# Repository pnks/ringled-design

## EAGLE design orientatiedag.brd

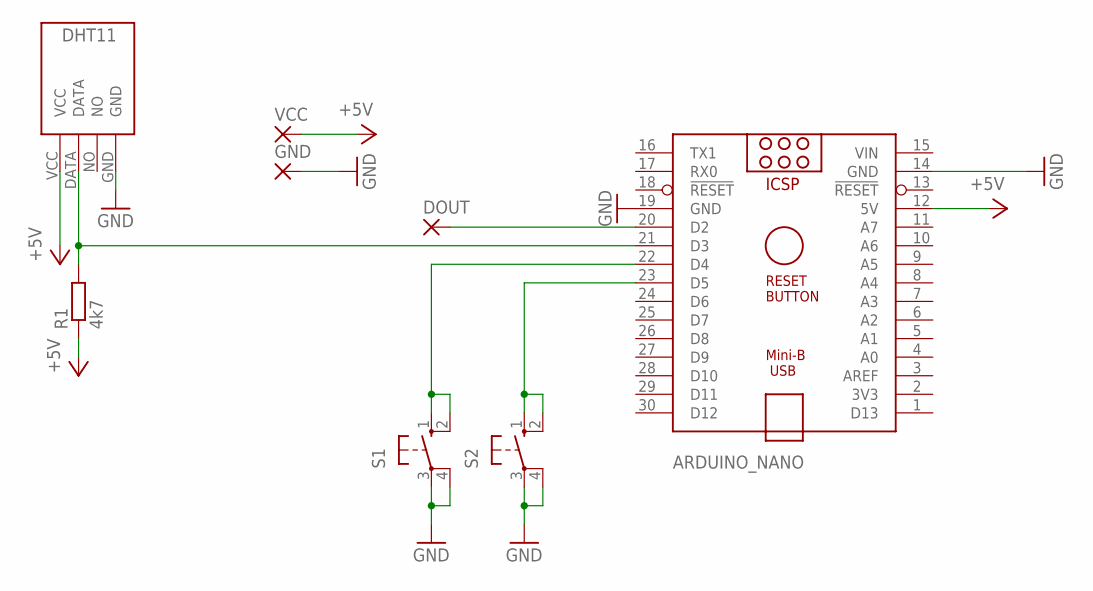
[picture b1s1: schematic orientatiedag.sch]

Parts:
ARDUINO_NANO: ARDUINO_NANO
DOUT: 2,15/1,0
GND: 2,15/1,0
R1: 4k7; 0207/7
S1, S2: 10-XX; B3F-10XX
U$1: DHT11-PION.
VCC: 2,15/1,0

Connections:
+5V: ARDUINO_NANO.12 (5V), R1.1, U$1.VCC, VCC.1
DHT-DATA: ARDUINO_NANO.21 (D3), R1.2, U$1.DATA
GND: ARDUINO_NANO.14 (GND), ARDUINO_NANO.19 (GND), GND.1, S1.3, S1.4 (P1), S2.3, S2.4 (P1), U$1.GND
unnamed: ARDUINO_NANO.22 (D4), S1.1 (S), S1.2 (S1)
unnamed: ARDUINO_NANO.23 (D5), S2.1 (S), S2.2 (S1)
unnamed: ARDUINO_NANO.20 (D2), DOUT.1
VIN: ARDUINO_NANO.15 (VIN)

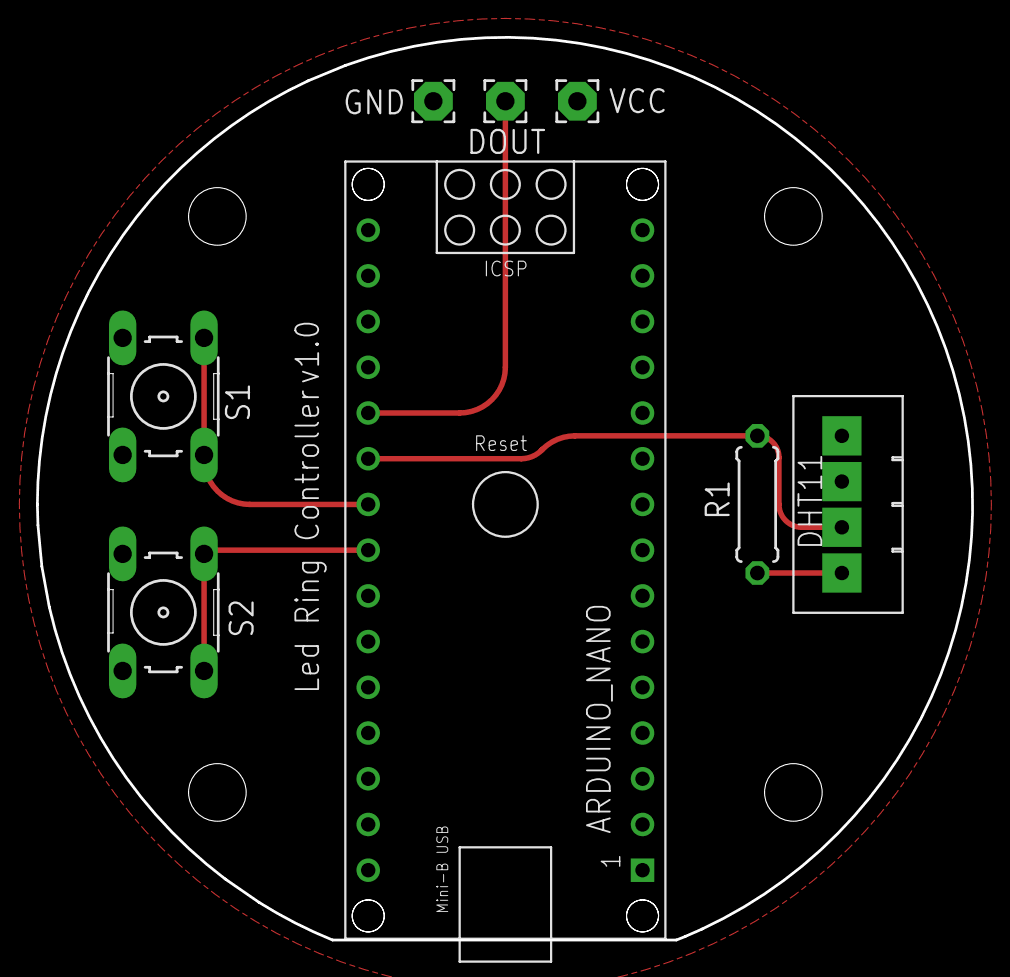
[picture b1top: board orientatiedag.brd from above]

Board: 2 copper layers, 52.0 x 50.1 mm, 8 parts (0 on the bottom side), 6 nets.
